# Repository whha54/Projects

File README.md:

# Self-Balancing-Robotic-Desk-Assistant-Scoot-Mk.-1-

A collection of files, code, and images involved in the development of Scoot Mk. 1.

# Overview
Scoot Mk.1 is a small self-balancing robotic desk assistant designed to be a companion for the user as they study or do work. Using buttons on the outside of its frame, the user can also use Scoot as a Pomodoro timer, helping with the user's productivity needs.

# Electronics Description
To develop the electronics for Scoot, I used the CAD tool KiCad to develop the schematic and footprint of the custom PCB. In this PCB, I used an STM32F411 microcontroller due to its high performance compared to the Arduino family of microcontrollers and its 512 KBytes of flash memory, giving me the plenty of space to write code and eliminating the need for external flash memory on the board. Peripherals are a USB-C 2.0 receptacle, ESD protection diode array, motor drivers, battery charger, LED display, accelerometer and gyroscope, an LDO, and 2 N20 motors with magnetic encoders. When making the footprint of the board, I used design techniques such as copper pours and via stitching to reduce the inductance and EMI of the board by reducing the current return loop area. I also made sure to minimize the distance of the USB D- and D+ differential pair and placed decoupling capacitors for every power pin of each IC as close as possible. I also used different trace widths for signal and power pins as thicker traces are needed for the amperage demands for power pins; I used 0.200 mm tracks for signal pins and 0.400 mm tracks for power pins.

# Frame and Software
I am currently in the process of creating the frame of Scoot and the code for Scoot. For the frame, I will use Autodesk Fusion360, and for the code, I plan to use a combination of STM32Cube IDE and Arduino IDE. STM32Cube IDE will allow me to interact directly with the microcontroller to assign pin functions. I will use the Arduino IDE to create the PID algorithm for self-balancing and the Pomodoro timer firmware.

# Future Iterations
- Replace Arduino IDE with C or C++ as programming knowledge expands
- Integrate obstacle-avoidance capabilities

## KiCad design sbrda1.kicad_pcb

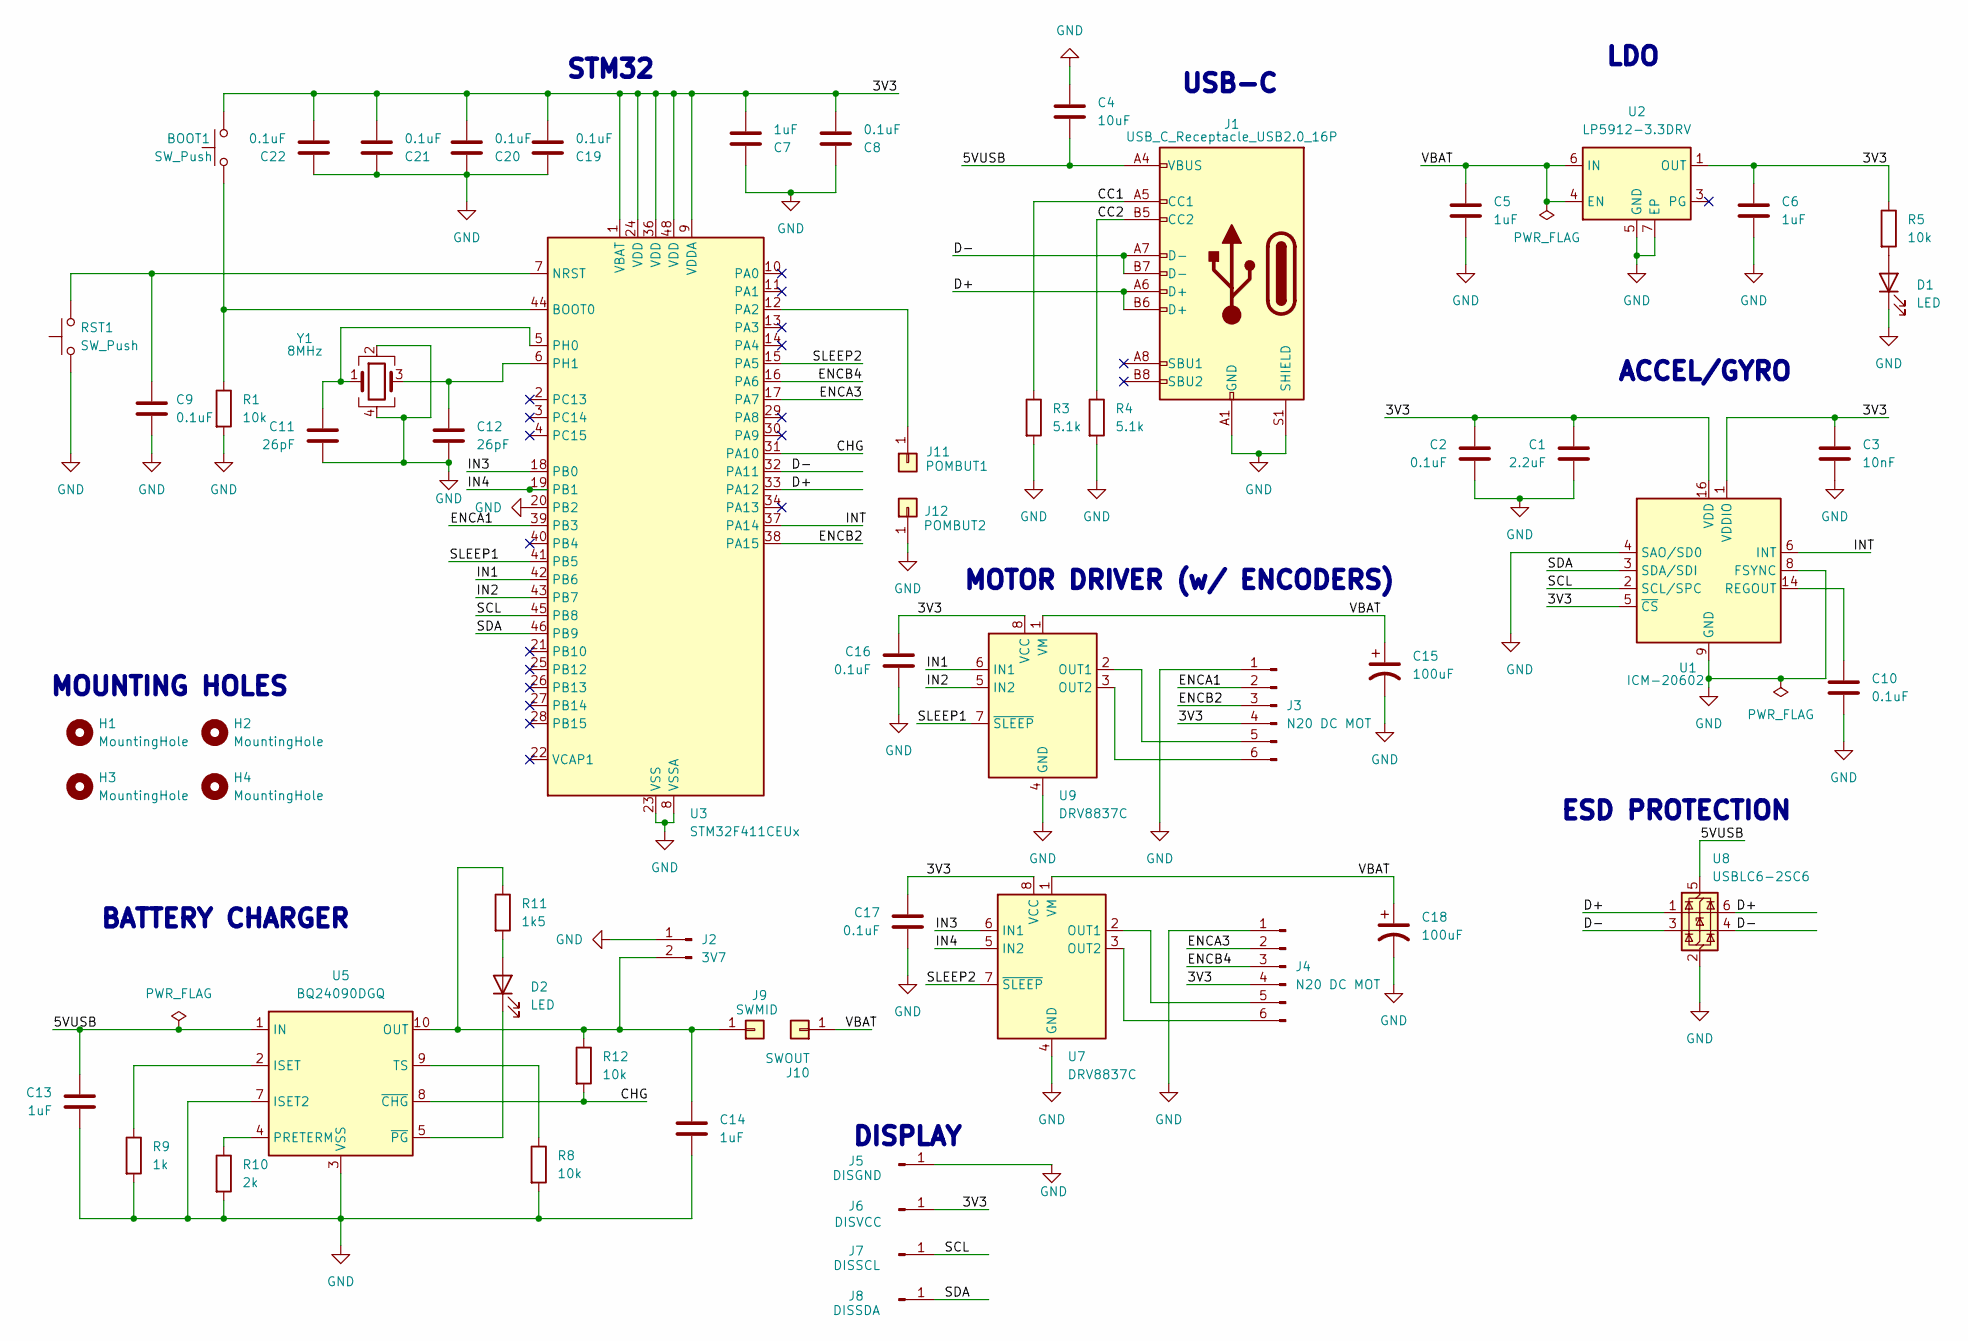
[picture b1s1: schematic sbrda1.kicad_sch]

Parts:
BOOT1: SW_Push; SW_SPST_EVQP2_ShortPushTravel_H2.1mm
C1: 2.2uF; C_0402_1005Metric
C2, C8, C9, C10, C16, C17, C19, C20, C21, C22: 0.1uF; C_0402_1005Metric
C3: 10nF; C_0402_1005Metric
C4: 10uF; C_0402_1005Metric
C5, C6, C7, C13, C14: 1uF; C_0402_1005Metric
C11, C12: 26pF; C_0402_1005Metric
C15, C18: 100uF; CP_Elec_6.3x7.7
D1, D2: LED; LED_0805_2012Metric
H1, H2, H3, H4: MountingHole; MountingHole_3.2mm_M3_ISO7380_Pad
J1: USB_C_Receptacle_USB2.0_16P; USB_C_Receptacle_GCT_USB4105-xx-A_16P_TopMnt_Horizontal
J2: 3V7; JST_PH_B2B-PH-K_1x02_P2.00mm_Vertical
J3, J4: N20 DC MOT; JST_SH_BM06B-SRSS-TB_1x06-1MP_P1.00mm_Vertical
J5: DISGND; SolderWirePad_1x01_SMD_1x2mm
J6: DISVCC; SolderWirePad_1x01_SMD_1x2mm
J7: DISSCL; SolderWirePad_1x01_SMD_1x2mm
J8: DISSDA; SolderWirePad_1x01_SMD_1x2mm
J9: SWMID; SolderWirePad_1x01_SMD_1.5x3mm
J10: SWOUT; SolderWirePad_1x01_SMD_1.5x3mm
J11: POMBUT1; SolderWirePad_1x01_SMD_1.5x3mm
J12: POMBUT2; SolderWirePad_1x01_SMD_1.5x3mm
R1, R5, R8, R12: 10k; R_0402_1005Metric
R3, R4: 5.1k; R_0402_1005Metric
R9: 1k; R_0402_1005Metric
R10: 2k; R_0402_1005Metric
R11: 1k5; R_0402_1005Metric
RST1: SW_Push; SW_SPST_EVQP2_ShortPushTravel_H2.1mm
U1: ICM-20602; LGA-16_3x3mm_P0.5mm_LayoutBorder3x5y
U2: LP5912-3.3DRV; WSON-6-1EP_2x2mm_P0.65mm_EP1x1.6mm_ThermalVias
U3: STM32F411CEUx; QFN-48-1EP_7x7mm_P0.5mm_EP5.6x5.6mm_ThermalVias
U5: BQ24090DGQ; HVSSOP-10-1EP_3x3mm_P0.5mm_EP1.57x1.88mm_ThermalVias
U7, U9: DRV8837C; WSON-8-1EP_2x2mm_P0.5mm_EP0.9x1.6mm_ThermalVias
U8: USBLC6-2SC6; SOT-23-6
Y1: 8MHz; Crystal_SMD_5032-4Pin_5.0x3.2mm

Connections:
/3V3: BOOT1.2, C1.1, C2.1, C3.1, C6.1, C7.2, C8.2, C16.1, C17.1, C19.2, C20.2, C21.2, C22.2, J3.4, J4.4, J6.1 (Pin_1_1), R5.1, U1.1 (VDDIO), U1.5 (~CS), U1.16 (VDD), U2.1 (OUT), U3.1 (VBAT), U3.9 (VDDA), U3.24 (VDD), U3.36 (VDD), U3.48 (VDD), U7.8 (VCC), U9.8 (VCC)
/5VUSB: C4.2, C13.1, J1.A4 (VBUS), J1.A9 (VBUS), J1.B4 (VBUS), J1.B9 (VBUS), U5.1 (IN), U8.5 (VBUS)
/CC1: J1.A5 (CC1), R3.1
/CC2: J1.B5 (CC2), R4.1
/CHG: R12.2, U3.31 (PA10), U5.8 (~CHG)
/D+: J1.A6 (D+), J1.B6 (D+), U3.33 (PA12), U8.1 (I/O1), U8.6 (I/O1)
/D-: J1.A7 (D-), J1.B7 (D-), U3.32 (PA11), U8.3 (I/O2), U8.4 (I/O2)
/ENCA1: J3.2, U3.39 (PB3)
/ENCA3: J4.2, U3.17 (PA7)
/ENCB2: J3.3, U3.38 (PA15)
/ENCB4: J4.3, U3.16 (PA6)
/IN1: U3.42 (PB6), U9.6 (IN1)
/IN2: U3.43 (PB7), U9.5 (IN2)
/IN3: U3.18 (PB0), U7.6 (IN1)
/IN4: U3.19 (PB1), U7.5 (IN2)
/INT: U1.6 (INT), U3.37 (PA14)
/SCL: J7.1 (Pin_1_1), U1.2 (SCL/SPC), U3.45 (PB8)
/SDA: J8.1 (Pin_1_1), U1.3 (SDA/SDI), U3.46 (PB9)
/SLEEP1: U3.41 (PB5), U9.7 (~SLEEP)
/SLEEP2: U3.15 (PA5), U7.7 (~SLEEP)
/VBAT: C5.1, C15.1, C18.1, J10.1 (Pin_1_1), U2.4 (EN), U2.6 (IN), U7.1 (VM), U9.1 (VM)
GND: C1.2, C2.2, C3.2, C4.1, C5.2, C6.2, C7.1, C8.1, C9.2, C10.2, C11.2, C12.2, C13.2, C14.2, C15.2, C16.2, C17.2, C18.2, C19.1, C20.1, C21.1, C22.1, D1.1 (K), J1.A1 (GND), J1.A12 (GND), J1.B1 (GND), J1.B12 (GND), J1.S1 (SHIELD), J2.1, J3.1, J4.1, J5.1 (Pin_1_1), J12.1 (Pin_1_1), R1.2, R3.2, R4.2, R8.2, R9.2, R10.2, RST1.1, U1.4 (SAO/SD0), U1.8 (FSYNC), U1.9 (GND), U1.10 (GND), U1.11 (GND), U1.12 (GND), U1.13 (GND), U1.15 (GND), U2.5 (GND), U2.7 (EP), U3.8 (VSSA), U3.20 (PB2), U3.23 (VSS), U3.35 (VSS), U3.47 (VSS), U3.49 (VSS), U5.3 (VSS), U5.7 (ISET2), U5.11 (VSS), U7.4 (GND), U7.9 (GND), U8.2 (GND), U9.4 (GND), U9.9 (GND), Y1.2, Y1.4
unnamed: D1.2 (A), R5.2
unnamed: D2.2 (A), R11.2
unnamed: D2.1 (K), U5.5 (~PG)
unnamed: C14.1, J2.2, J9.1 (Pin_1_1), R11.1, R12.1, U5.10 (OUT)
unnamed: J3.5, U9.2 (OUT1)
unnamed: J3.6, U9.3 (OUT2)
unnamed: J4.5, U7.2 (OUT1)
unnamed: J4.6, U7.3 (OUT2)
unnamed: J11.1 (Pin_1_1), U3.12 (PA2)
unnamed: C10.1, U1.14 (REGOUT)
unnamed: BOOT1.1, R1.1, U3.44 (BOOT0)
unnamed: C9.1, RST1.2, U3.7 (NRST)
unnamed: C11.1, U3.5 (PH0), Y1.1
unnamed: C12.1, U3.6 (PH1), Y1.3
unnamed: R9.1, U5.2 (ISET)
unnamed: R10.1, U5.4 (PRETERM)
unnamed: R8.1, U5.9 (TS)

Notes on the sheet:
LDO
STM32
MOUNTING HOLES
MOTOR DRIVER (w/ ENCODERS)
ACCEL/GYRO
ESD PROTECTION
USB-C
BATTERY CHARGER
DISPLAY

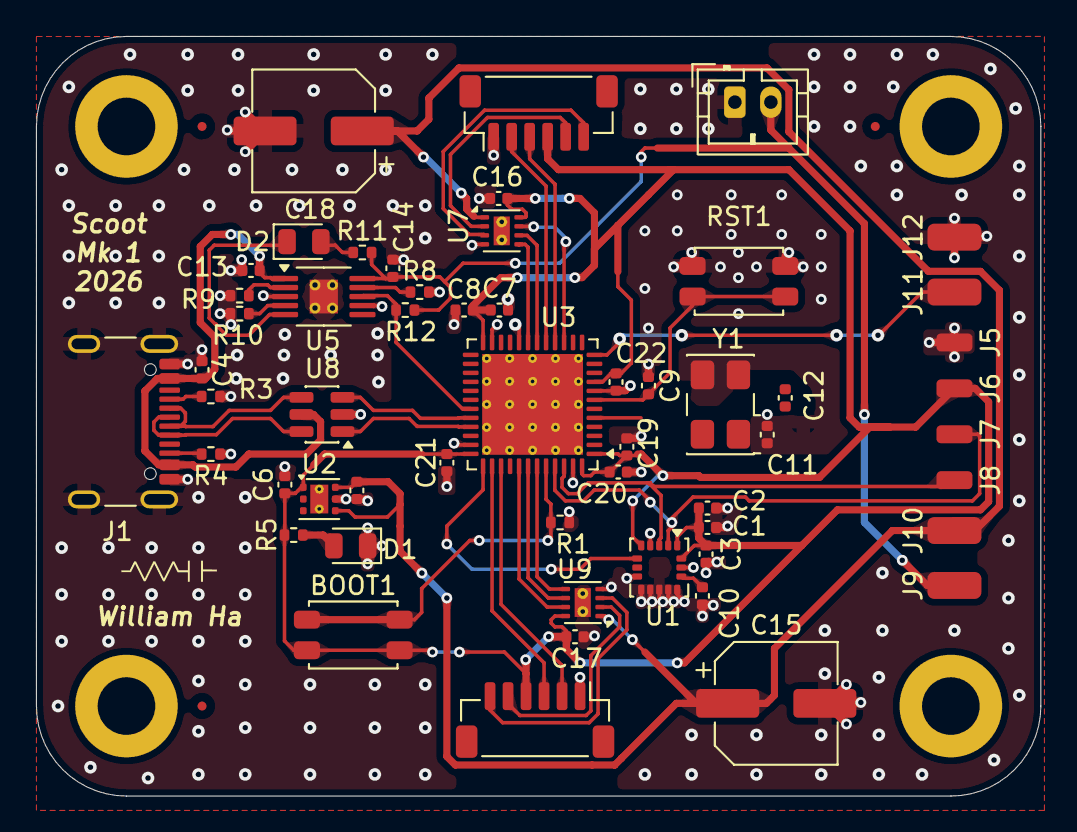
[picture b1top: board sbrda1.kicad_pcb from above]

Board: 2 copper layers, 55.8 x 42.2 mm, 59 parts (0 on the bottom side), 39 nets.

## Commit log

2026-05-06 Revise README for Scoot Mk. 1 project overview
    Updated README to include details about Scoot Mk. 1 project, its electronics, frame, software, and future iterations.
